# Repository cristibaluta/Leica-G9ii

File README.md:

# Leica G9II

> The internals of a Panasonic Lumix G9II inside a Leica M-style body — featuring custom CNC-machined parts and redesigned flex cables and buttons.

---

## 📸 Overview

This project is an attempt to make a beautiful small camera from a Lumix G9II body. The camera is focused on street photography and has missing buttons and features.

If you are an expert in any relevant field and see mistakes you are welcome to open issues for discussion, my only qualification to do this is that I was into electronics a long time ago.

---

## What's Included

- `/CADs/` – STEP files for CNC machining, including threads sheets
- `/FPCBs/` – Schematics and gerber files for the flex cables
- `/Datasheets/` – Some datasheets from used components
- `/BOM/` – List of extra items and purchase links

---

## Materials (BOM)

| Part                | Description                      | Notes |
|---------------------|----------------------------------|-------|
| Top plate           | Milled aluminum                  | Included in CADs |
| Base plate          | Milled aluminum                  |  |
| Front               | Milled aluminum                  |  |
| Back                | Milled aluminum                  |  |
| Heatsink            | Milled copper                    |  |
| Flex cable          | Internal routing rework          | Included in FPCBs |
| Screws              | M1.6 and M2                      | Refer to threads sheets in CADs |
| Body (G9II)         | Donor camera                     ||

---

## Build Instructions

> ⚠️ Advanced DIY skills required: electronics, soldering, disassembly without breaking, modifying original parts
> ⚠️ WIP

1. Disassemble Lumix G9II (see [https://www.youtube.com/@CameraSurgery])
2. Machine or print parts from `/CADs/`
3. Print flex cables from `/FPCBs/`
4. Install mount, lens release button
5. Install shutter
6. Install sensor
7. Install front lever and battery flex cable
8. Install heatsink
9. Install mainboard
10. Install top plate dials and flex cables
11. Install back buttons and flex cable
12. Install screen
13. Install viewfinder
14. Install wifi module
15. Assemble
16. Add leatherete
17. Install front lever

---

## Parts removed

1. Lens release push detector (not sure what it was doing beside displaying some info on the screen). There is not enough space to add this push detector
2. The following buttons: ISO-WB, front custom buttons

---

## TO DO:
- The dials are too lose
- The buttons are too short
- Thread missing from the lever clicker
- Remove back wheel
- Dials gaskets too thin (0.5mm), must be wider (1mm)
- Front and back could be extended up and down for better strength

---

## Licence

This project is licensed under the CERN Open Hardware Licence Version 2 – Permissive (CERN-OHL-P-2.0).

---

## 💬 Credits

Created by [Cristian Baluta]  
Youtube: [https://www.youtube.com/@CameraSurgery]

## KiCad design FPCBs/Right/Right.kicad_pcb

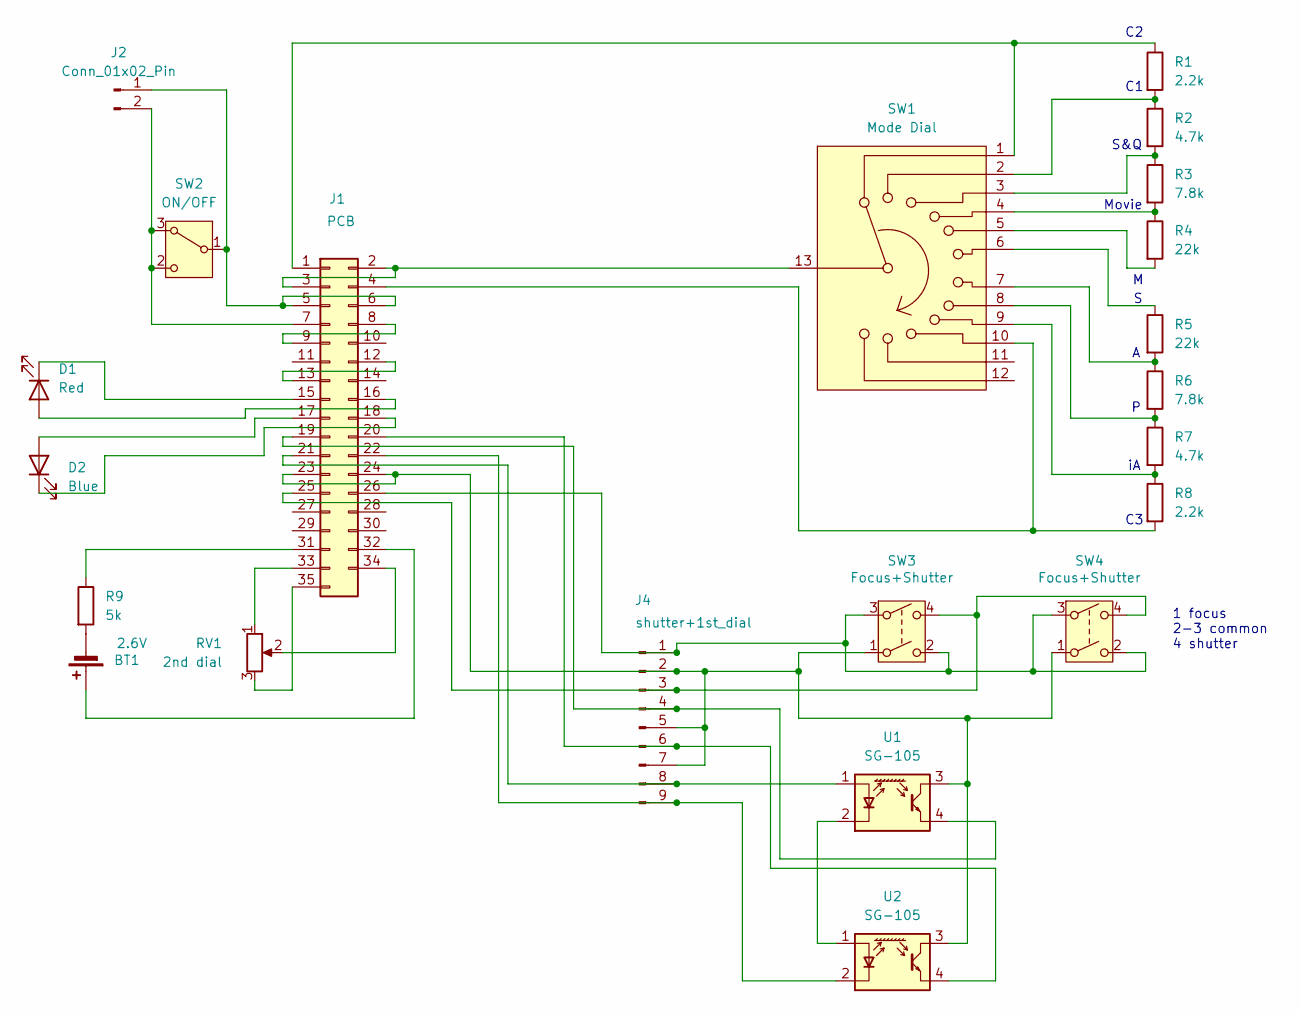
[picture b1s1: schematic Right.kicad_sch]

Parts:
BT1: 2.6V; Battery_Cell
D1: Red; LED
D2: Blue; LED
J1: PCB; FPC-2Rows-35Pins-0.5mm
J2: Conn_01x02_Pin; Connector-Screw-2Pins
J4: shutter+1st_dial; Connector-2Rows-9Pins-0.60mm
R1, R8: 2.2k; R_0603
R2, R7: 4.7k; R_0603
R3, R6: 7.8k; R_0603
R4, R5: 22k; R_0603
R9: 5k; R_0603
RV1: 2nd dial; 2nd_dial
SW1: Mode Dial; Switch_Modes
SW2: ON/OFF; Switch_ON_OFF
SW3: Focus+Shutter; Shutter_Canon
SW4: Focus+Shutter; Shutter_Olympus
U1, U2: SG-105; Opto_Switch

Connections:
unnamed: BT1.1 (+), J1.32
unnamed: BT1.2 (-), R9.2
unnamed: D1.2 (A), J1.16
unnamed: D1.1 (K), J1.15
unnamed: D2.2 (A), J1.17
unnamed: D2.1 (K), J1.18
unnamed: J1.1, R1.1, SW1.1
unnamed: J1.2, J1.3, SW1.13
unnamed: J1.4, R8.2, SW1.10
unnamed: J1.5, J1.6, J2.1, SW2.1 (B)
unnamed: J1.7, J2.2, SW2.2 (C), SW2.3 (A)
unnamed: J1.8, J1.9
unnamed: J1.12, J1.13
unnamed: J1.19, J4.4, U1.4 (E)
unnamed: J1.20, J4.6, U2.4 (E)
unnamed: J1.21, J4.8, U1.1 (A)
unnamed: J1.22, J4.9, U2.2 (K)
unnamed: J1.23, J1.24, J4.2, J4.5, J4.7, SW3.1, SW4.1, U1.3 (C), U2.3 (C)
unnamed: J1.25, J4.3, SW3.4, SW4.4
unnamed: J1.26, J4.1, SW3.2, SW3.3, SW4.2, SW4.3
unnamed: J1.31, R9.1
unnamed: J1.33, RV1.1
unnamed: J1.34, RV1.2
unnamed: J1.35, RV1.3
unnamed: R1.2, R2.1, SW1.2
unnamed: R2.2, R3.1, SW1.3
unnamed: R3.2, R4.1, SW1.4
unnamed: R4.2, SW1.5
unnamed: R5.1, SW1.6
unnamed: R5.2, R6.1, SW1.7
unnamed: R6.2, R7.1, SW1.8
unnamed: R7.2, R8.1, SW1.9
unnamed: U1.2 (K), U2.1 (A)

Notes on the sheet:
1 focus 2-3 common 4 shutter
S&Q
Movie

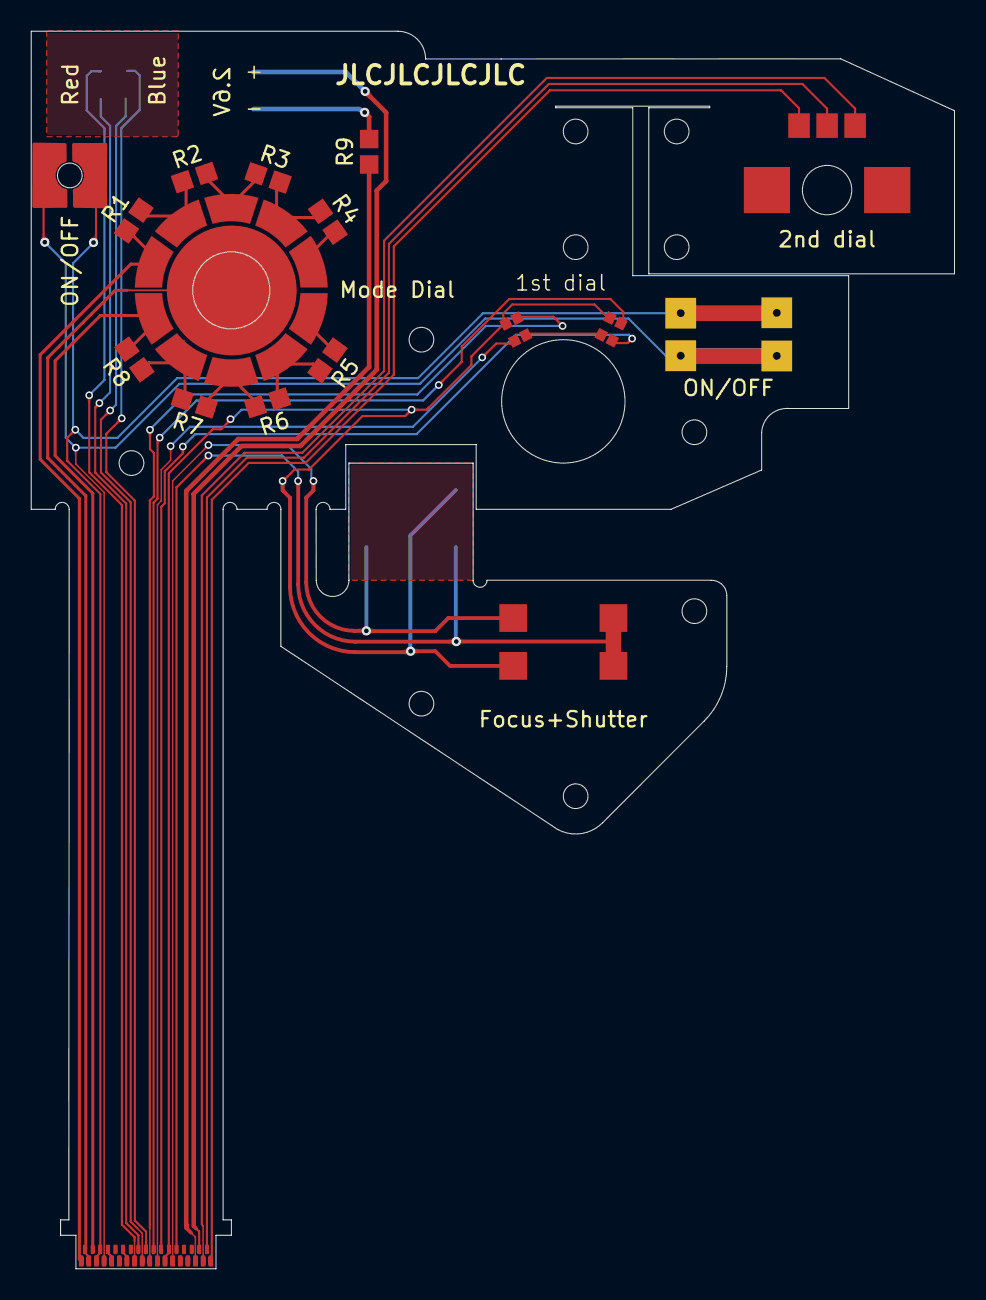
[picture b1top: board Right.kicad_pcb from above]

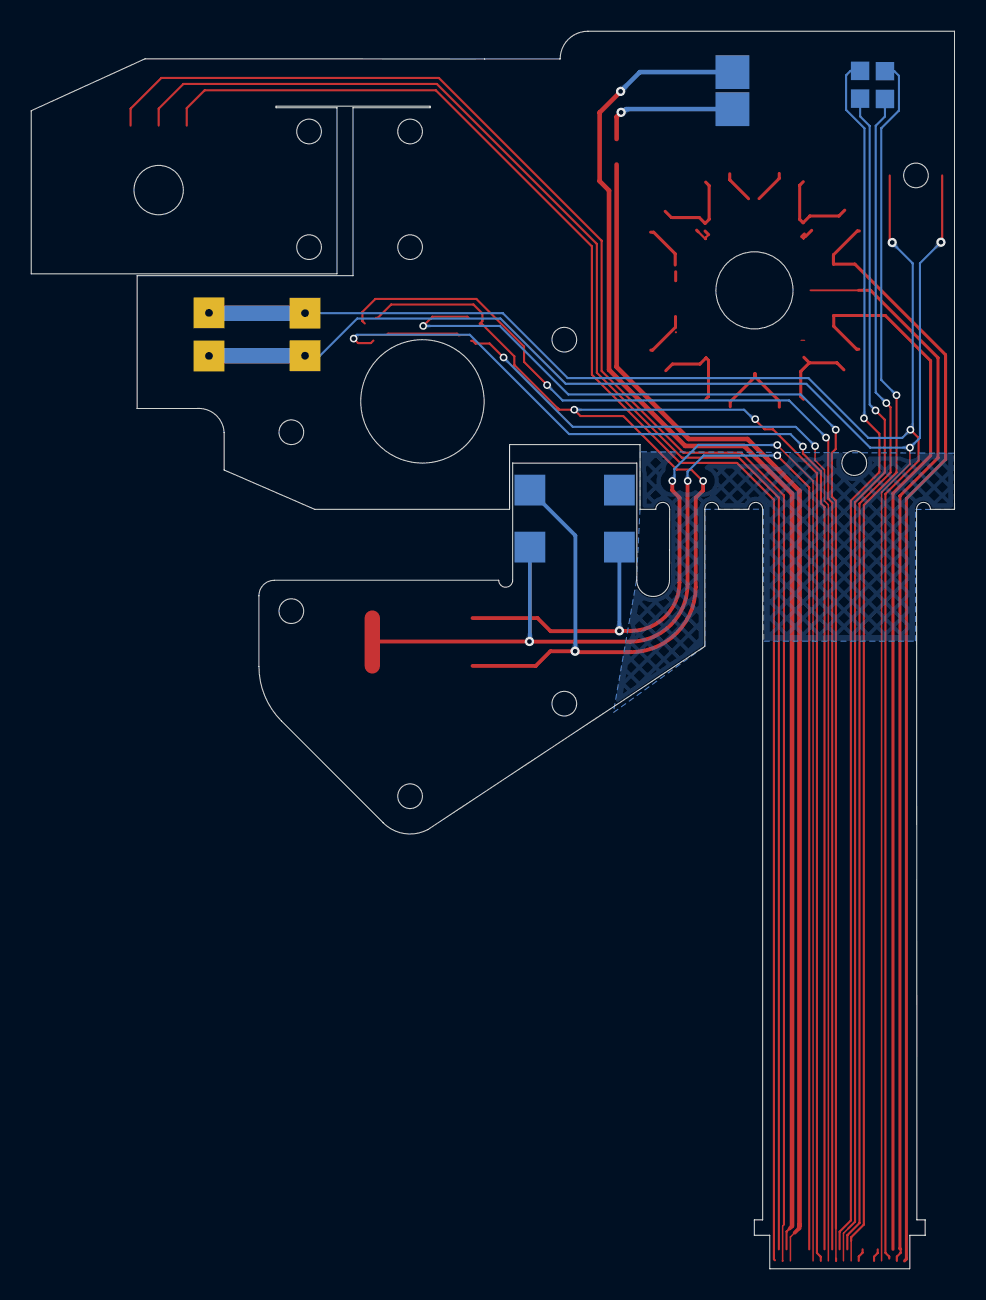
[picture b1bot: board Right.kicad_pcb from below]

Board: 2 copper layers, 59.9 x 80.2 mm, 21 parts (5 on the bottom side), 33 nets.

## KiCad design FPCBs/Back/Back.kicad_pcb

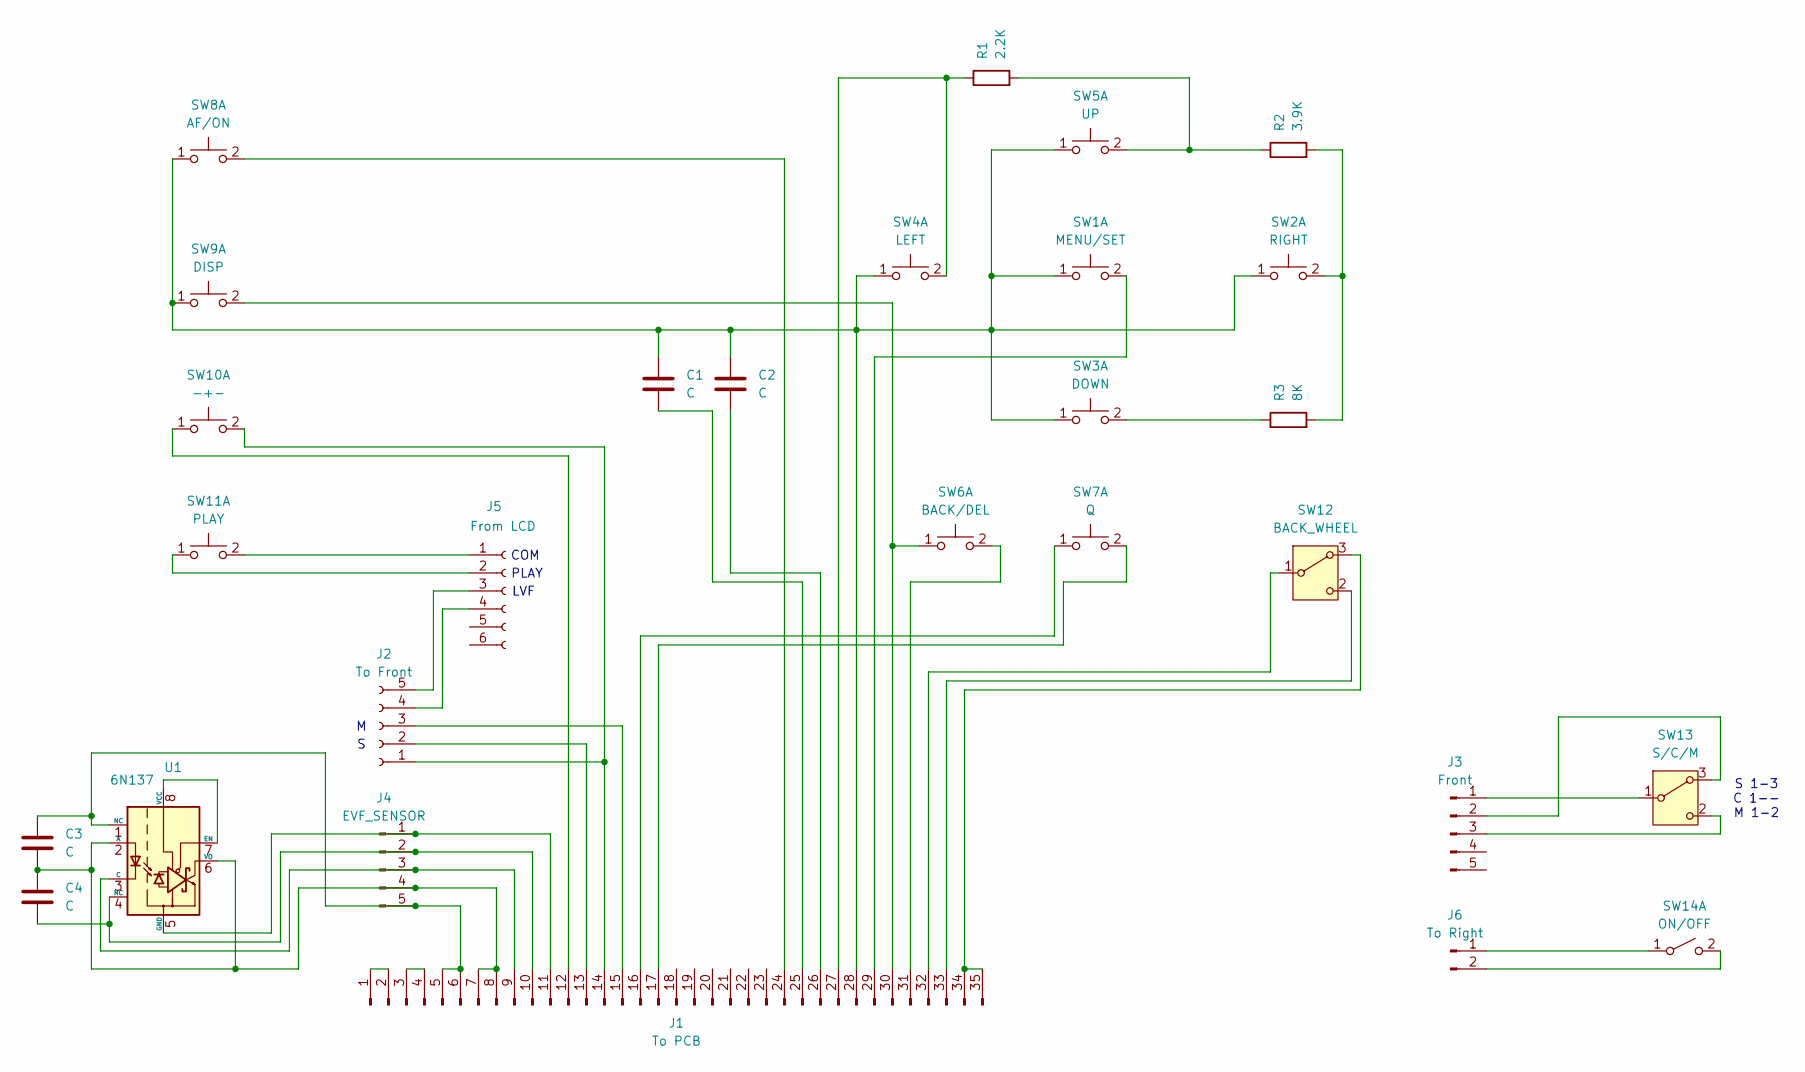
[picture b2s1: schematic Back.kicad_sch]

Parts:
C1, C2, C3, C4: C; R_0603
J1: To PCB; FPC-2Rows-35Pins-0.5mm
J2: To Front; Connector-1Row-5Pins-0.40mm
J3: Front; FPC-1Row-5Pins-0.40mm
J4: EVF_SENSOR; FPC-1Row-7Pins-0.40mm
J5: From LCD; Connector-1Row-6Pins-0.40mm
J6: To Right; Connector-Screw-2Pins
R1: 2.2K; R_0603
R2: 3.9K; R_0603
R3: 8K; R_0603
SW1: MENU/SET; Push_Button
SW2: RIGHT; Push_Button
SW3: DOWN; Push_Button
SW4: LEFT; Push_Button
SW5: UP; Push_Button
SW6: BACK/DEL; Push_Button
SW7: Q; Push_Button
SW8: AF/ON; Push_Button
SW9: DISP; Push_Button
SW10: -+-; Push_Button
SW11: PLAY; Push_Button
SW12: BACK_WHEEL; back_dial
SW13: S/C/M; Switch_Detection_Bidirectional
SW14: ON/OFF; Switch_Detection
U1: 6N137; Optocoupler_EVF

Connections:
unnamed: J1.1, J1.2
unnamed: J1.3, J1.4
unnamed: C3.1, J1.5, J1.6, J4.5, U1.1 (NC)
unnamed: C3.2, C4.1, J1.7, J1.8, J4.4, U1.2 (A), U1.6 (VO)
unnamed: J1.9, J4.3, U1.3 (C)
unnamed: C4.2, J1.10, J4.2, U1.4 (NC)
unnamed: J1.11, J4.1, U1.5 (GND)
unnamed: J1.12, SW10.1 (C)
unnamed: J1.13, J2.2
unnamed: J1.14, J2.1, SW10.2 (D)
unnamed: J1.15, J2.3
unnamed: J1.16, SW7.1 (C)
unnamed: J1.17, SW7.2 (D)
unnamed: J1.24, SW8.2 (D)
unnamed: C1.2, J1.25
unnamed: C2.2, J1.26
unnamed: J1.27, R1.1, SW4.2 (D)
unnamed: C1.1, C2.1, J1.28, SW1.1 (C), SW2.1 (C), SW3.1 (C), SW4.1 (C), SW5.1 (C), SW8.1 (C), SW9.1 (C)
unnamed: J1.29, SW1.2 (D)
unnamed: J1.30, SW6.1 (C), SW9.2 (D)
unnamed: J1.31, SW6.2 (D)
unnamed: J1.32, SW12.1 (B)
unnamed: J1.33, SW12.2 (C)
unnamed: J1.34, J1.35, SW12.3 (A)
unnamed: J2.4, J5.4
unnamed: J2.5, J5.3
unnamed: J3.1, SW13.1 (B)
unnamed: J3.2, SW13.3 (A)
unnamed: J3.3, SW13.2 (C)
unnamed: J5.1, SW11.2 (D)
unnamed: J5.2, SW11.1 (C)
unnamed: J6.1, SW14.1 (A)
unnamed: J6.2, SW14.2 (B)
unnamed: R2.2, R3.2, SW2.2 (D)
unnamed: R3.1, SW3.2 (D)
unnamed: R1.2, R2.1, SW5.2 (D)
unnamed: U1.7 (EN), U1.8 (VCC)

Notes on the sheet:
PLAY
COM
S 1-3 C 1-- M 1-2
LVF

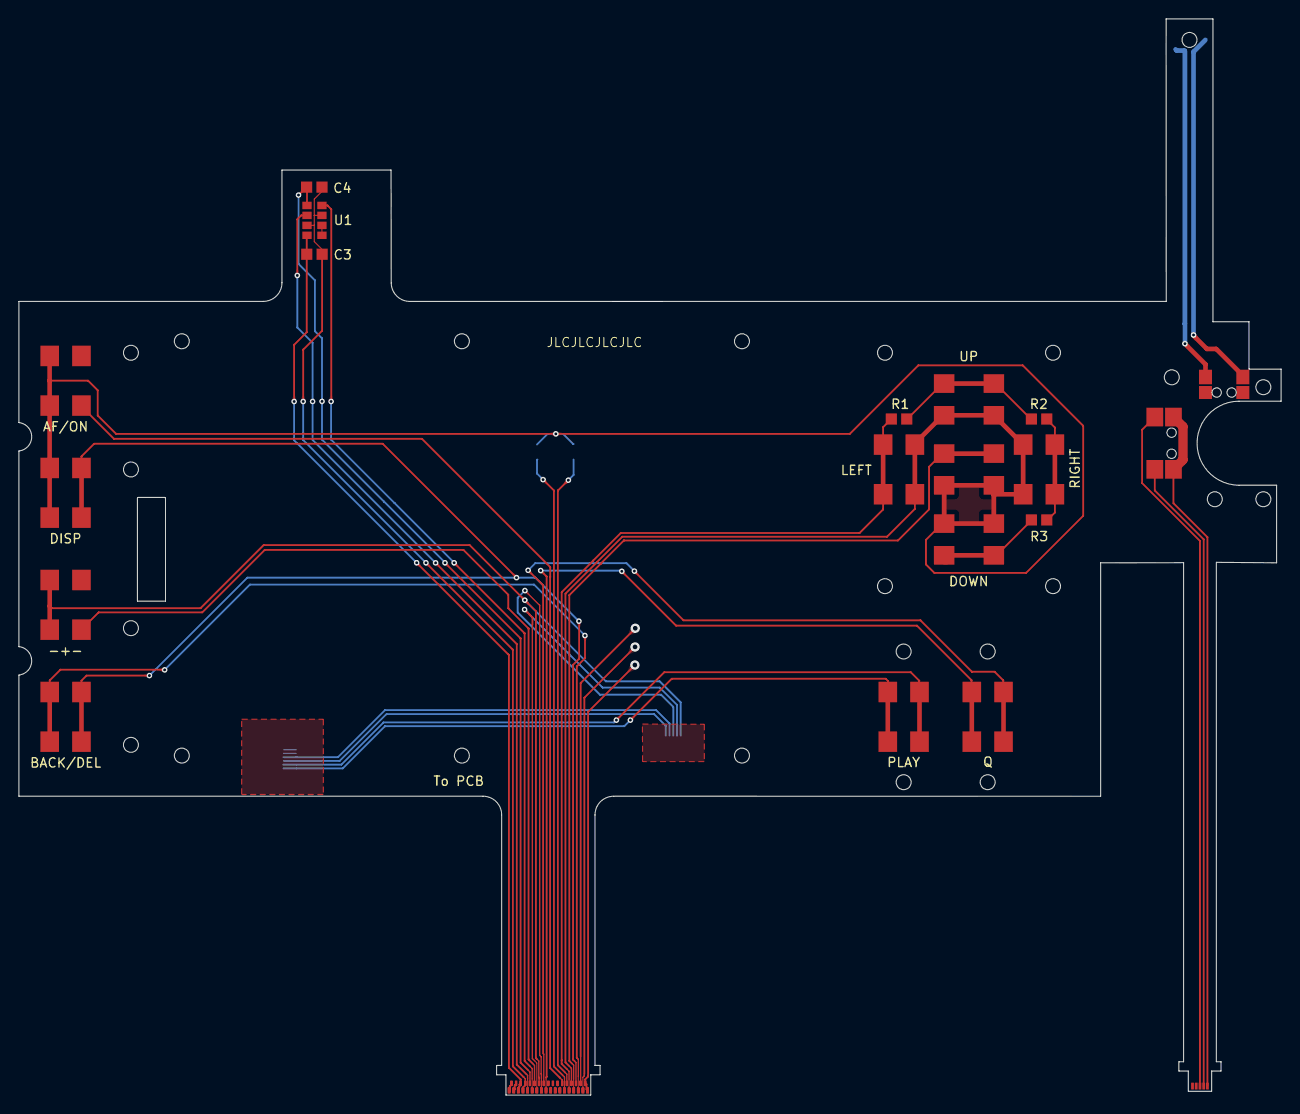
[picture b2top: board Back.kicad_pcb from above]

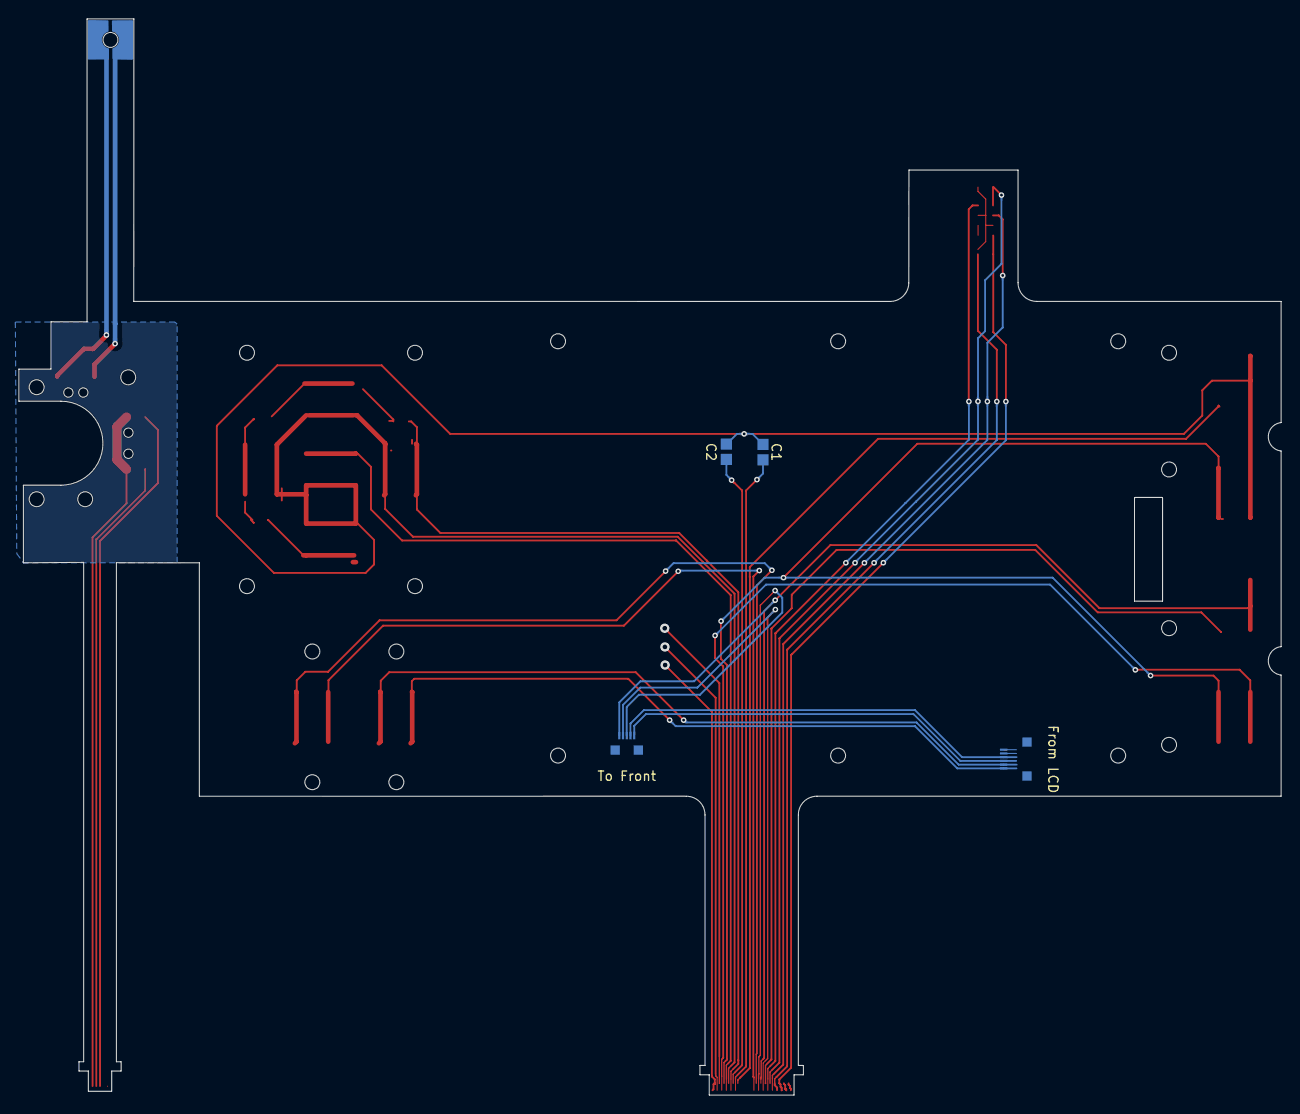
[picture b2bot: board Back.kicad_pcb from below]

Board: 2 copper layers, 135.2 x 115.3 mm, 26 parts (5 on the bottom side), 35 nets.

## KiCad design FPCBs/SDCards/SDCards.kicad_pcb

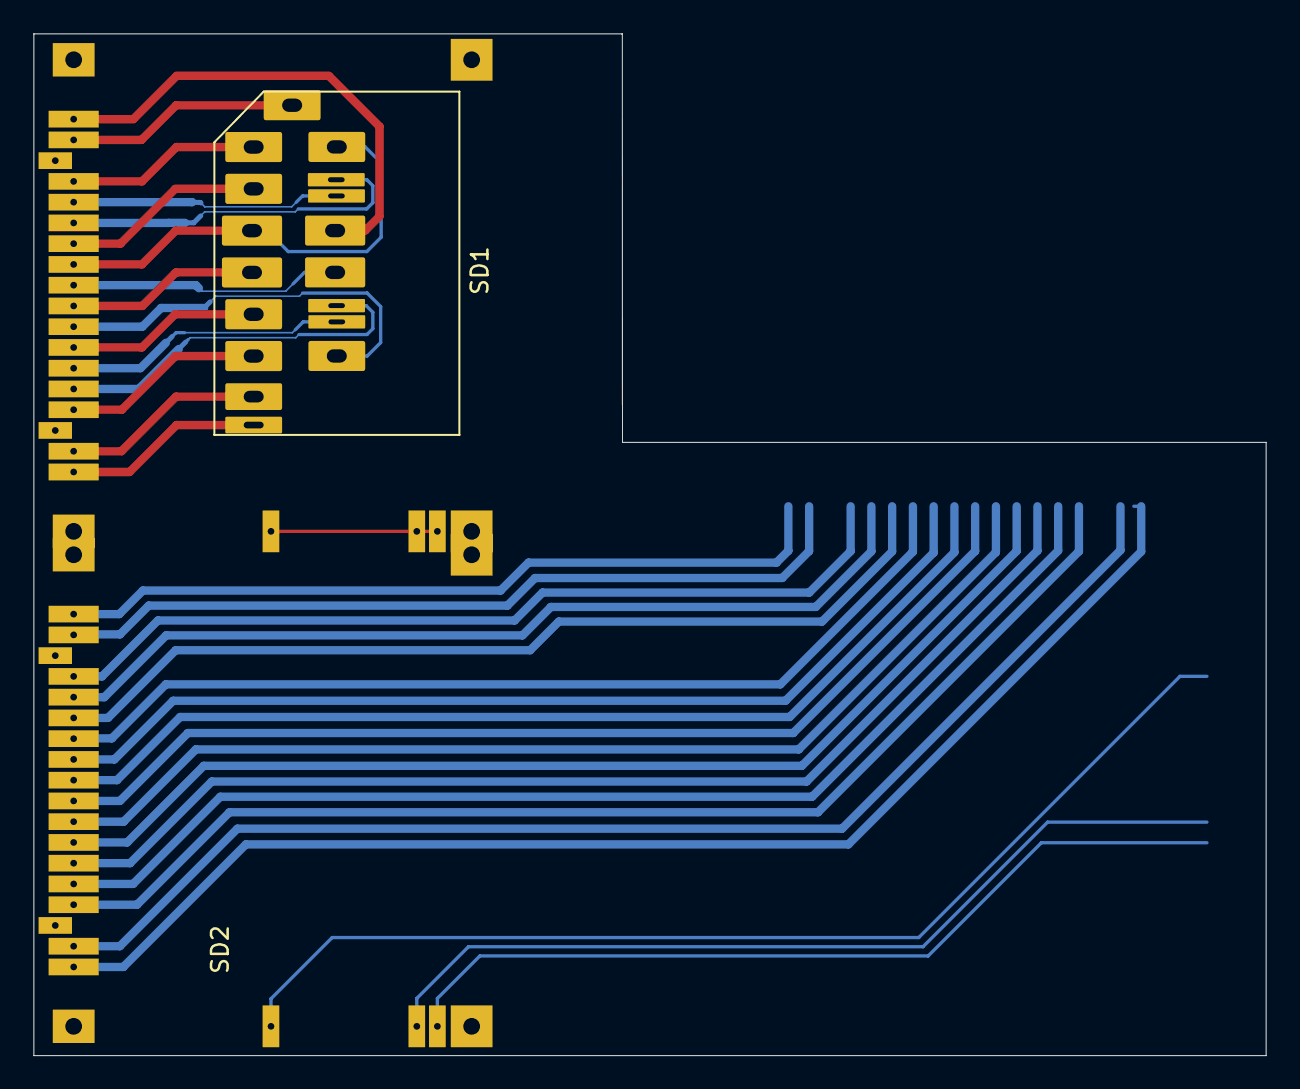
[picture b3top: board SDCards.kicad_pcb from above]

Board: 2 copper layers, 73.7 x 61.1 mm, 4 parts (1 on the bottom side), 37 nets.

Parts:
J1: SD1; SD_Card_Socket_UHS-II_Extender
J2: SD1; SD_Card_Chip_UHS-II
J3: SD2; SD_Card_Socket_UHS-II_Extender
J4: SD2; SD_Card_Socket_UHS-II_HTK_AXA573062

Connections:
unnamed: J1.CD (CARD_DETECT), J1.COM (COMMON), J1.WP (WRITE_PROTECT)
unnamed: J1.1 (CD/DAT3), J2.1 (CD/DAT3)
unnamed: J1.5 (CLK), J2.5 (CLK)
unnamed: J1.2 (CMD), J2.2 (CMD)
unnamed: J1.11 (D0+), J2.11 (D0+)
unnamed: J1.12 (D0-), J2.12 (D0-)
unnamed: J1.16 (D1+), J2.16 (D1+)
unnamed: J1.15 (D1-), J2.15 (D1-)
unnamed: J1.7 (DAT0), J2.7 (DAT0)
unnamed: J1.8 (DAT1), J2.8 (DAT1)
unnamed: J1.9 (DAT2), J2.9 (DAT2)
unnamed: J1.17 (Name), J2.17 (Name)
unnamed: J1.SH (SHIELD), J3.SH (SHIELD), J4.SH (SHIELD)
unnamed: J1.14 (VDD2), J2.14 (VDD2)
unnamed: J1.4 (VDD), J2.4 (VDD)
unnamed: J1.3 (VSS1), J2.3 (VSS1), J2.10 (VSS3)
unnamed: J1.6 (VSS2), J2.6 (VSS2)
unnamed: J1.13 (VSS4), J2.13 (VSS4)
unnamed: J3.CD (CARD_DETECT), J4.CD (CARD_DETECT)
unnamed: J3.1 (CD/DAT3), J4.1 (CD/DAT3)
unnamed: J3.5 (CLK), J4.5 (CLK)
unnamed: J3.2 (CMD), J4.2 (CMD)
unnamed: J3.COM (COMMON), J4.COM (COMMON)
unnamed: J3.11 (D0+), J4.11 (D0+)
unnamed: J3.12 (D0-), J4.12 (D0-)
unnamed: J3.16 (D1+), J4.16 (D1+)
unnamed: J3.15 (D1-), J4.15 (D1-)
unnamed: J3.7 (DAT0), J4.7 (DAT0)
unnamed: J3.8 (DAT1), J4.8 (DAT1)
unnamed: J3.9 (DAT2), J4.9 (DAT2)
unnamed: J3.17 (Name), J4.17 (Name)
unnamed: J3.14 (VDD2), J4.14 (VDD2)
unnamed: J3.4 (VDD), J4.4 (VDD)
unnamed: J3.3 (VSS1), J4.3 (VSS1)
unnamed: J3.6 (VSS2), J4.6 (VSS2)
unnamed: J3.13 (VSS4), J4.13 (VSS4)
unnamed: J3.WP (WRITE_PROTECT), J4.WP (WRITE_PROTECT)

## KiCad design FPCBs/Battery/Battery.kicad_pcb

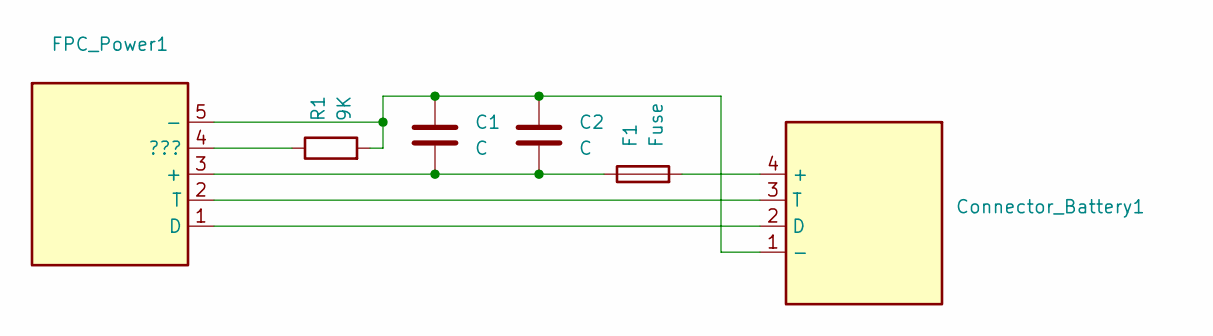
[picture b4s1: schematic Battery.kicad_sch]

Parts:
C1, C2: C; R_2x1mm
Connector_Battery1: Connector_Battery
F1: Fuse; R_2x1mm
FPC_Power1: FPC_Power
R1: 9K; R_2x1mm

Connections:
unnamed: Connector_Battery1.4 (+), F1.2
unnamed: C1.1, C2.1, Connector_Battery1.1 (-), FPC_Power1.5 (-), R1.2
unnamed: Connector_Battery1.2 (D), FPC_Power1.1 (D)
unnamed: Connector_Battery1.3 (T), FPC_Power1.2 (T)
unnamed: C1.2, C2.2, F1.1, FPC_Power1.3 (+)
unnamed: FPC_Power1.4 (???), R1.1

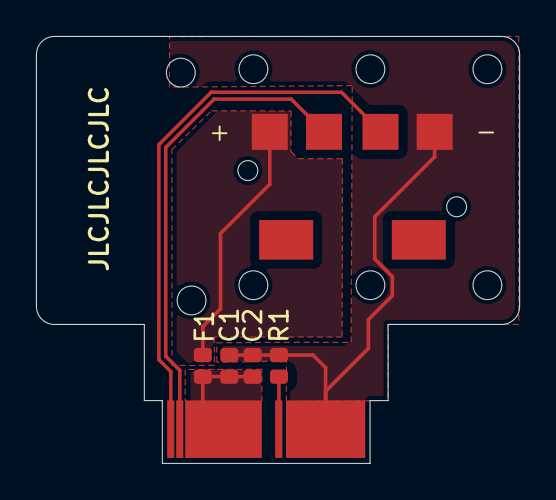
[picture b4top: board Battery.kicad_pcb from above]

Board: 2 copper layers, 26.8 x 23.7 mm, 6 parts (0 on the bottom side), 6 nets.

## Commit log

2025-06-11 Add image
2025-06-19 Add battery fpcb
2025-06-21 Battery fpcb
2025-06-21 Cleanup
2025-06-21 Add more boards
2025-06-23 Add driving modes switch
2025-06-29 Export buttons and dials
2025-06-29 Connect the clickers
2025-07-02 Finish schematic
2025-07-05 Add footprints
2025-07-09 Extend fpc size
2025-07-09 Add connector
2025-07-13 Adjust the 35 pins connector
2025-07-27 Update the back pcb
2025-07-27 Fix 4 pins connector
2025-07-27 Update to kicad 9
2025-08-04 Add sd card
2025-08-06 Add pad mask
2025-08-06 Add gitignore
2025-08-07 Add masks to the battery pcb
2025-08-07 Add EVF extender FPCB
2025-08-07 Add curved tracks
2025-08-08 Add stiffeners
2025-08-08 Fixes on the left side FPC
2025-08-09 Move leds to Right board
2025-08-09 Add extra switch for on/off
2025-08-10 Fixes for the back pcb
2025-08-10 Export
2025-08-11 Update USBC
2025-08-11 Fix the usbc extender
2025-08-11 Rename folder
2025-08-12 Add copper tot he back side
2025-08-12 Add back copper
2025-08-13 Add gyro holder 3D model
2025-08-13 Decrease the second row pads width in the fpc connector 35pins
2025-08-28 Add Canon shutter footprint
2025-09-07 Fix the buttons pins
2025-09-08 Fix back wheel footprint
2025-09-09 Fixes to Back board
2025-09-10 Fixes to back pcb
2025-09-10 Move fpc to left
2025-09-11 Fixes to the right pcb
2025-09-11 Add serpentines
2025-09-11 Add through holes for on off switch
2025-09-12 Fix small battery footprint
2025-09-13 Fixes on the shutter
2025-09-13 Move evf sensor to left
2025-09-14 Second shutter FPC
2025-09-14 Fix back wheel
2025-09-15 Fixes
2025-09-15 Add 1st dial connector
2025-09-15 Generate Gerbers
2025-10-27 Update image
2025-11-13 Rewire one side of the evf connector to the back side
    Add Lumix logo
2025-12-02 Add engravings
2025-12-18 Correct evf distance
2025-12-18 Fix stiffeners
2026-01-07 Add second shutter
2026-01-08 Add EVF optocoupler
2026-01-08 Fix battery fpc size
2026-01-08 Fix left fpcb
2026-01-09 sd card
2026-01-11 Add second power button
2026-01-11 Fix positions on back fpcb
2026-01-13 Improve the back fpcb
2026-01-17 Add front lever flex cable
2026-01-20 Fix switch detectors footprints
2026-01-23 Adjustments for evf and right fpcb
2026-01-24 Fix sd card
2026-01-25 Fix spacings and pads
2026-01-26 Gerbers
2026-01-26 Fix connectors
2026-01-26 Add holes to switch detectors
2026-01-26 Fix masks
2026-01-27 Enlarge pcb to allow bending
2026-02-24 Export new Gerbers and CADs
2026-02-24 Export the mask
2026-02-25 Arrange buttons differently to meet minimum size requirement by cnc
